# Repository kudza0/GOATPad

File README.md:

# GOATPad
My first attempt at a macropad for Hack Club. Designed to use with for hotkeys on CAD (fusion 360) and digital art (krita).

This entire project took 15+ hours, most of which was spent navigating and battling fusion 360. Designing the PCB was the most straightforward process, despite 3 iterations of it being created during the process I pulled through. All in all this was a fun project, and I learnt a lot about the CAD and PCB design workflow. 

(PS. The actual thing has key caps...)

### Featuring:
- Xiao RP2040 Microcontroller
- 12 keys (3x4 Matrix PCB)
- SSD1306 0.91" OLED display
- An imaculate 3D printed case designed by yours truly
- Silkscreen easter egg (iykyk)

<h2> Schematic</h2>

<h2> PCB Traces</h2>

<h2> Case</h2>
The full case .STEP file had to be compressed to a ZIP file for me to upload to GitHub...

### Firmware
I made it using QMK (all files included), however it has yet to be tested...

### BOM
- 1x Xiao RP2040
- 1x Case (2x 3D Printed parts)
- 1x 0.91" 128x32 SSD1306 OLED Display
- 12x Cherry MX Switches
- 12x DSA Caps
- 12x 1N4148 DO-35 Diodes
- 4x M3x16mm Screws
- 4x M3x5mx4mm Heat Inserts

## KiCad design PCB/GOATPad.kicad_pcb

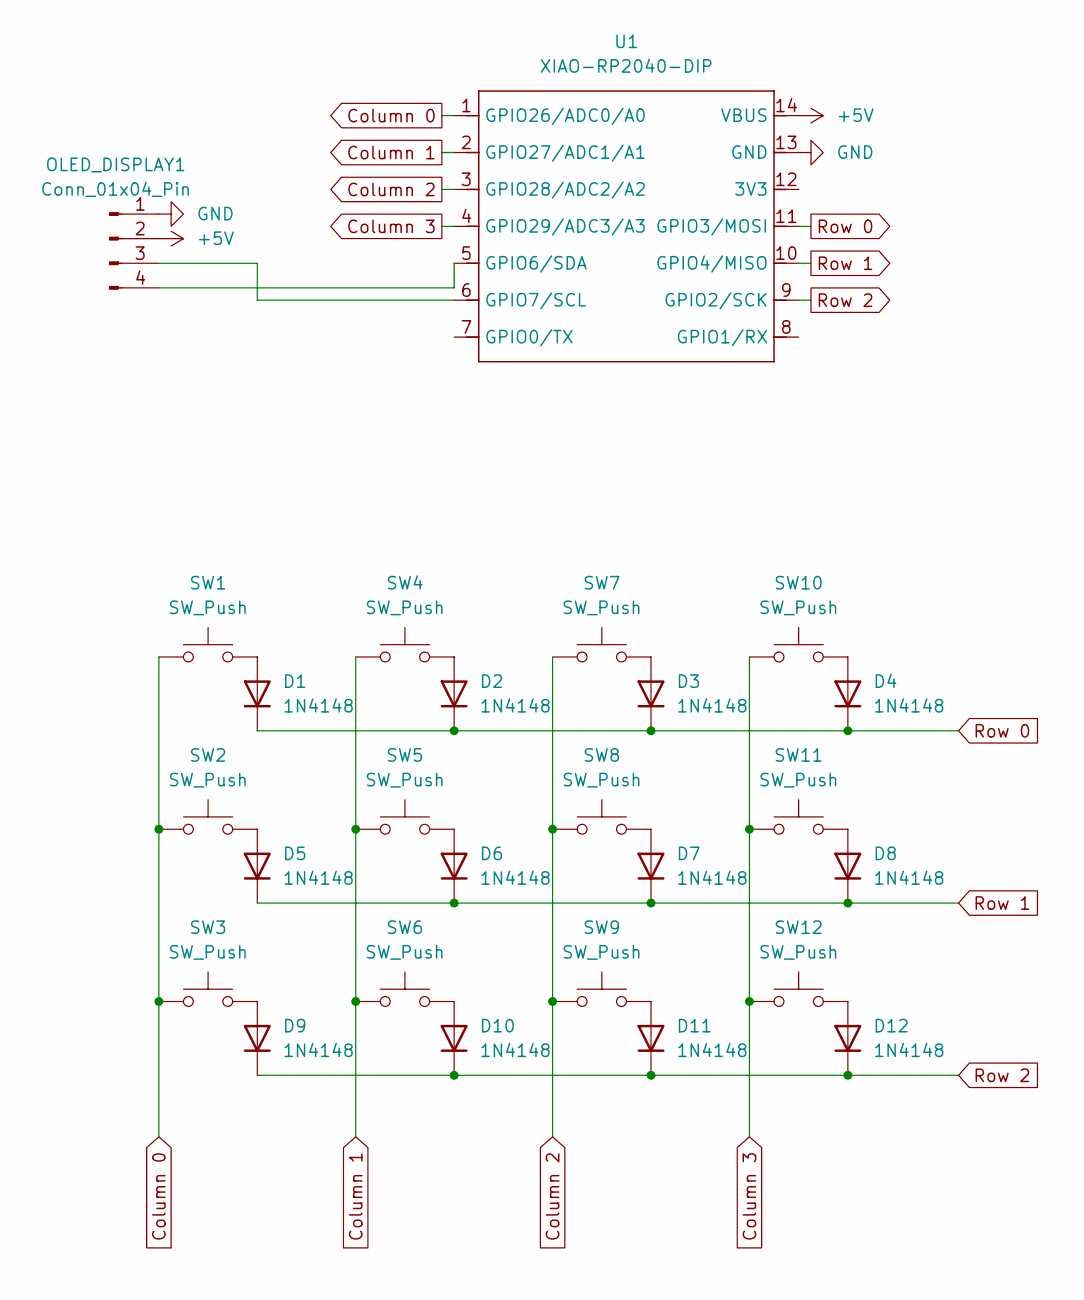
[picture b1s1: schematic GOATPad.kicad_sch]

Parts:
D1, D2, D3, D4, D5, D6, D7, D8, D9, D10, D11, D12: 1N4148; D_DO-35_SOD27_P7.62mm_Horizontal
OLED_DISPLAY1: Conn_01x04_Pin; SSD1306-0.91-OLED-4pin-128x32
SW1, SW2, SW3, SW4, SW5, SW6, SW7, SW8, SW9, SW10, SW11, SW12: SW_Push; SW_Cherry_MX_1.00u_PCB
U1: XIAO-RP2040-DIP

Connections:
+5V: OLED_DISPLAY1.2, U1.14 (VBUS)
Column 0: SW1.1, SW2.1, SW3.1, U1.1 (GPIO26/ADC0/A0)
Column 1: SW4.1, SW5.1, SW6.1, U1.2 (GPIO27/ADC1/A1)
Column 2: SW7.1, SW8.1, SW9.1, U1.3 (GPIO28/ADC2/A2)
Column 3: SW10.1, SW11.1, SW12.1, U1.4 (GPIO29/ADC3/A3)
GND: OLED_DISPLAY1.1, U1.13 (GND)
unnamed: D1.2 (A), SW1.2
unnamed: D2.2 (A), SW4.2
unnamed: D3.2 (A), SW7.2
unnamed: D4.2 (A), SW10.2
unnamed: D5.2 (A), SW2.2
unnamed: D6.2 (A), SW5.2
unnamed: D7.2 (A), SW8.2
unnamed: D8.2 (A), SW11.2
unnamed: D9.2 (A), SW3.2
unnamed: D10.2 (A), SW6.2
unnamed: D11.2 (A), SW9.2
unnamed: D12.2 (A), SW12.2
unnamed: OLED_DISPLAY1.3, U1.6 (GPIO7/SCL)
unnamed: OLED_DISPLAY1.4, U1.5 (GPIO6/SDA)
Row 0: D1.1 (K), D2.1 (K), D3.1 (K), D4.1 (K), U1.11 (GPIO3/MOSI)
Row 1: D5.1 (K), D6.1 (K), D7.1 (K), D8.1 (K), U1.10 (GPIO4/MISO)
Row 2: D9.1 (K), D10.1 (K), D11.1 (K), D12.1 (K), U1.9 (GPIO2/SCK)

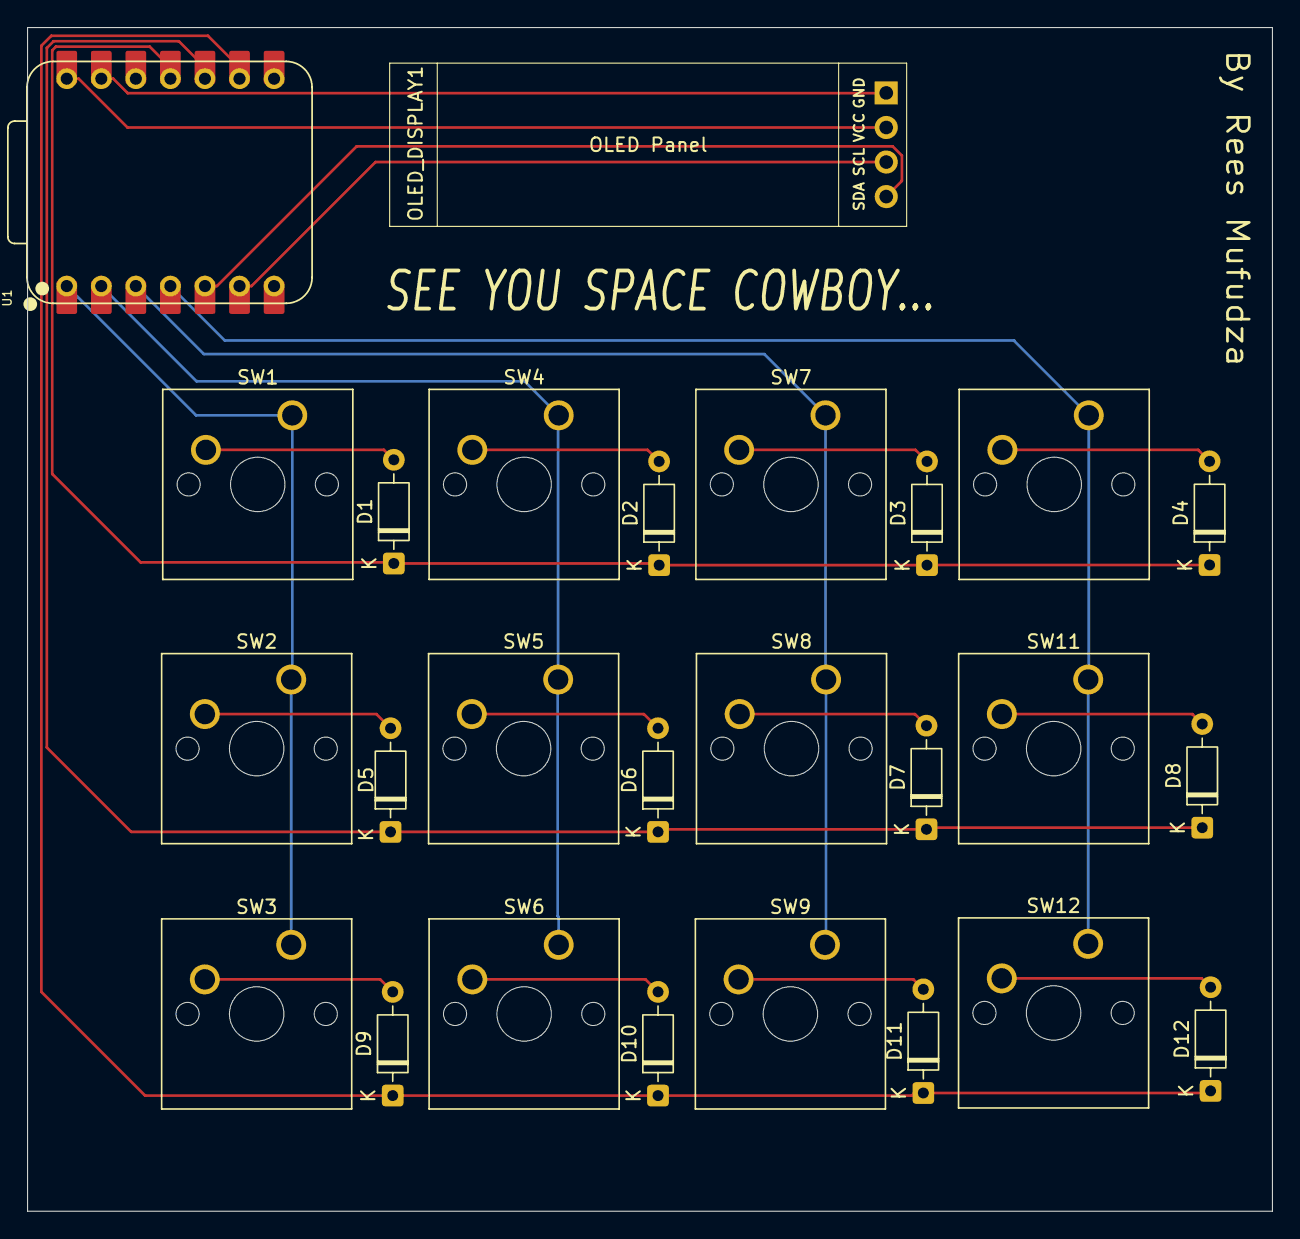
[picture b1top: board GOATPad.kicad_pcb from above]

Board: 2 copper layers, 91.5 x 87.0 mm, 26 parts (0 on the bottom side), 23 nets.

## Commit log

2026-02-12 Upload images
2026-02-17 Upload firmware
2026-02-17 Move GOATPad.zip to CAD/GOATPad.zip
